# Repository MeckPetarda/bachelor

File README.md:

# Lighthouse — UHF RFID attendance system

Bachelor's thesis project:
**Embedded Implementation of an Attendance System for Integration into an Enterprise Application**

**Author:** Jakub Hloušek
**Supervisor:** Ing. Michal Bastl, Ph.D.
**Institution:** Brno University of Technology, Faculty of Mechanical Engineering
**Academic year:** 2025/26

## Overview

Lighthouse is a passive, hands-free attendance tracking system using UHF RFID technology (860–960 MHz) to detect
employees at 2–3 meter range without any user interaction. Tags are detected through bags, purses, and pockets. Two
paired Lighthouse units at an entrance determine traversal direction (entry vs. exit) and report events to a central
server, which integrates with Navigo3 — a Czech HR/enterprise application by Navigo Solutions s.r.o.

The system is designed to be cost-effective, low-maintenance, and self-contained with its own REST API, while also
supporting external integration.

## Architecture

```text
[UHF RFID Tag] ──► [Lighthouse Unit A] ──► MQTT ──► [Server] ──► [Navigo3 API]
                   [Lighthouse Unit B] ──►          │
                                                    ├── PostgreSQL
                                                    ├── REST API
                                                    └── SolidJS Dashboard
```

The project consists of three major components:

### Firmware (`src/lighthouse/`)

ESP32-based firmware written in C using ESP-IDF and FreeRTOS. Runs on custom PCBs with YPD-R300 UHF RFID reader modules.

Key features:

- UHF RFID tag reading via UART (command 0x89 real-time inventory)
- IR sensor-triggered scan windows
- WiFi provisioning via captive portal (AP mode with DNS redirect)
- MQTT communication with QoS 2 and Last Will & Testament
- NTP time synchronization with explicit quality tracking (`synced`, `estimated`, `relative`)
- Offline event caching on LittleFS (2 MB partition, ~43k events)
- Battery monitoring via ADC
- Health telemetry reporting
- AES-encrypted credential storage in dedicated NVS partition

Firmware source modules: `lighthouse.c`, `rfid_reader.c`, `my_mqtt_client.c`, `io_controller.c`, `battery_monitor.c`,
`time_sync.c`, `wifi_manager.c`, `offline_event_logger.c`, and the `wifi_provisioning` component.

### Server (`src/server/`)

BunJS/TypeScript backend with an embedded MQTT broker.

| Layer    | Technology | Purpose                           |
| -------- | ---------- | --------------------------------- |
| Runtime  | Bun        | TypeScript execution, test runner |
| HTTP     | Hono       | REST API framework                |
| Database | PostgreSQL | Persistent storage                |
| ORM      | Drizzle    | Type-safe queries, migrations     |
| MQTT     | Aedes      | Embedded broker (no external dep) |
| Frontend | SolidJS    | Dashboard SPA                     |
| Build    | Vite       | Frontend bundling                 |

REST API provides endpoints for lighthouses, groups, events, scans, and users. WebSocket support for real-time dashboard
updates. Retention cleanup scheduler for old data. Event sweeper for processing closed RFID scan clusters.

### Hardware (`circuits/lighthouse/`)

Custom PCB designed in KiCad. Board v2 has been sent to fabrication (PCBWay).

Key components: ESP32-WROOM-32, YPD-R300 UHF RFID module, TP4056 charging module (USB-C), SX1308 DC-DC boost converter,
CP2102 USB-UART bridge, 18650 battery holder, IR sensor for scan triggering.

### Dashboard (`src/server/src/web/`)

SolidJS single-page application served by the backend. Pages for lighthouse management, groups, raw events, processed
events, and users.

## Repository structure

```text
.
├── src/
│   ├── lighthouse/          # ESP32 firmware (ESP-IDF/FreeRTOS, C)
│   │   ├── main/            # Core firmware modules
│   │   ├── components/      # WiFi provisioning component (captive portal, settings)
│   │   ├── partitions.csv   # Flash partition layout
│   │   └── sdkconfig        # ESP-IDF configuration
│   └── server/              # Backend + frontend (BunJS, TypeScript, SolidJS)
│       ├── src/
│       │   ├── api/         # Hono REST routes and middleware
│       │   ├── database/    # Drizzle ORM schema and client
│       │   ├── mqtt/        # Aedes broker, topic handlers
│       │   ├── services/    # Event processing, algorithms, Navigo3 integration
│       │   └── web/         # SolidJS dashboard (pages, components, stores)
│       └── tests/           # Bun test suite
├── circuits/lighthouse/     # KiCad PCB project (schematic, board, components)
├── docs/                    # Datasheets, API docs, design documents
├── tasks/                   # Agent task documents (implementation specs)
├── logbook/                 # Development logs
├── write/                   # Thesis LaTeX/Typst sources
├── scripts/                 # Utility scripts (NTP setup)
└── presentation/            # Presentation materials
```

## Prerequisites

### Firmware

- [ESP-IDF](https://docs.espressif.com/projects/esp-idf/en/latest/esp32/get-started/) (v5.x)
- ESP32 development board or Lighthouse custom PCB
- USB-UART connection (CP2102 or external adapter)

### Server

- [Bun](https://bun.sh/) runtime
- PostgreSQL (with a database named `attendance`)
- [chrony](https://chrony-project.org/) NTP server (optional, for ESP32 time sync on LAN — config in
  `src/server/config/chrony.conf`)

## Building & flashing the firmware

### 1. set up ESP-IDF environment

```bash
. /home/kuba/code/esp-idf/export.sh
```

### 2. build

```bash
cd src/lighthouse
idf.py build
```

### 3. flash

The firmware uses a custom partition table. All four binaries must be flashed to their correct offsets:

```bash
esptool --chip esp32 -p /dev/ttyUSB0 -b 921600 \
  --before=no-reset --after=no-reset --no-stub \
  write-flash --flash-mode dio --flash-freq 40m --flash-size detect \
  0x1000 ./build/bootloader/bootloader.bin \
  0x8000 ./build/partition_table/partition-table.bin \
  0x360000 ./build/spiffs.bin \
  0x10000 ./build/lighthouse.bin
```

**Flash layout** (from `partitions.csv`):

| Offset   | Size    | Partition        | Purpose                             |
| -------- | ------- | ---------------- | ----------------------------------- |
| 0x1000   | —       | Bootloader       | ESP-IDF managed                     |
| 0x8000   | 4 KB    | Partition table  | Partition metadata                  |
| 0x9000   | 24 KB   | `nvs`            | System NVS (WiFi calibration, etc.) |
| 0xF000   | 4 KB    | `phy_init`       | RF calibration data                 |
| 0x10000  | 1280 KB | `factory`        | Application firmware                |
| 0x150000 | 2 MB    | `offline_events` | LittleFS — offline RFID event cache |
| 0x350000 | 16 KB   | `nvs_settings`   | Encrypted WiFi/MQTT credentials     |
| 0x360000 | 64 KB   | `spiffs`         | Setup page HTML (captive portal)    |

### 4. monitor serial output

```bash
idf.py -p /dev/ttyUSB0 monitor
```

Or with custom baud rate:

```bash
idf.py -p /dev/ttyUSB0 -b 115200 monitor
```

Exit monitor with `Ctrl+]`.

## Running the server

### 1. install dependencies

```bash
cd src/server
bun install
```

### 2. configure database

The server expects PostgreSQL at `postgresql://postgres:postgres@localhost:5432/attendance` by default. Override with
the `DATABASE_URL` environment variable.

Run Drizzle migrations:

```bash
bunx drizzle-kit push
```

### 3. start the server

Development mode (with file watching):

```bash
bun run dev
```

This starts the HTTP server (with embedded MQTT broker) and serves the API.

### 4. build and serve the dashboard

Development (Vite dev server with HMR):

```bash
bun run dev:web
```

Production build:

```bash
bun run build:web
```

The production build is served automatically by the backend at the root path.

### 5. run tests

```bash
bun test
```

Individual test suites:

```bash
bun test tests/mqtt-broker.test.ts
bun test tests/event-processing.test.ts
bun test tests/api-routes.test.ts
```

## Device setup (First boot)

1. Power on the Lighthouse unit. If no WiFi credentials are stored, it enters setup mode automatically.
2. Long-press BUTTON1 (5 seconds) to force entry into setup mode at any time.
3. Connect to the `Lighthouse-Setup` WiFi network from a phone or computer.
4. A captive portal opens automatically on iOS, Android, Windows, and macOS. On Linux, navigate to `http://192.168.4.1`
   manually.
5. Enter WiFi SSID, password, and MQTT broker IP/port on the setup page.
6. The device tests connectivity, saves encrypted credentials to NVS, and reboots into normal operation.

## Debugging

### Firmware debug tips

- **Serial log levels**: Controlled via `sdkconfig`. Default is `DEBUG`. Use `idf.py menuconfig` under
  `Component config → Log output` to change.
- **RF debug mode**: Compile with `#define RF_DEBUG_MODE` in `lighthouse.c` to enable power sweep, parameter queries,
  and continuous RSSI inventory. This replaces normal operation entirely.
- **Button controls in normal mode**: BUTTON1 starts/stops scanning; BUTTON2 prints statistics to serial.
- **LED indicators**: WiFi status LED, MQTT status LED, and RFID scanning status LED provide visual feedback on GPIO
  pins.
- **Offline event log**: Events are cached in LittleFS at the `offline_events` partition. The log uses a ring buffer
  with CRC32 integrity checks per record.
- **Time quality**: Check serial output for `TIME_QUALITY_SYNCED`, `TIME_QUALITY_ESTIMATED`, or `TIME_QUALITY_NONE` —
  events are tagged with this quality in MQTT payloads as the `timeBasis` field.

### Server debug tips

- **Server logs**: Structured logging via the internal logger. Increase verbosity by editing `src/utils/logger.ts`.
- **MQTT debugging**: The embedded Aedes broker runs alongside the HTTP server. Use any MQTT client (e.g.,
  `mosquitto_sub`) to subscribe to `lighthouse/#` topics for raw traffic inspection.
- **Database inspection**: Connect directly to PostgreSQL. Key tables: `raw_scans` (immutable audit log),
  `processed_events` (derived entry/exit), `lighthouses`, `tag_assignments`, `users`.
- **Integration test**: `bun run scripts/integration-test.ts` exercises the MQTT → database pipeline.

### NTP setup

The server machine doubles as the NTP server for Lighthouse devices on the LAN. Install and configure chrony using the
provided config:

```bash
sudo cp src/server/config/chrony.conf /etc/chrony/chrony.conf
sudo systemctl restart chrony
```

Alternatively, use the setup script:

```bash
sudo bash scripts/setup-ntp.sh
```

## Documentation

- `docs/` — Component datasheets (ESP32, R300 RFID module, TP4056, CP2102, etc.)
- `docs/navigo_api.md` — Navigo3 REST API documentation
- `docs/phase2_event_processing_plan.md` — Direction detection algorithm design
- `docs/phase4_integration.md` — Navigo3 integration plan
- `logbook/` — Chronological development logs
- `tasks/` — Structured implementation task documents

## License

See [LICENSE](LICENSE).

---

esp.py build

esptool --chip esp32 -p /dev/ttyUSB0 -b 921600 --before=no-reset --after=no-reset --no-stub write-flash --flash-mode dio
--flash-freq 40m --flash-size detect 0x1000 ./build/bootloader/bootloader.bin 0x8000
./build/partition_table/partition-table.bin 0x360000 ./build/spiffs.bin 0x10000 ./build/lighthouse.bin

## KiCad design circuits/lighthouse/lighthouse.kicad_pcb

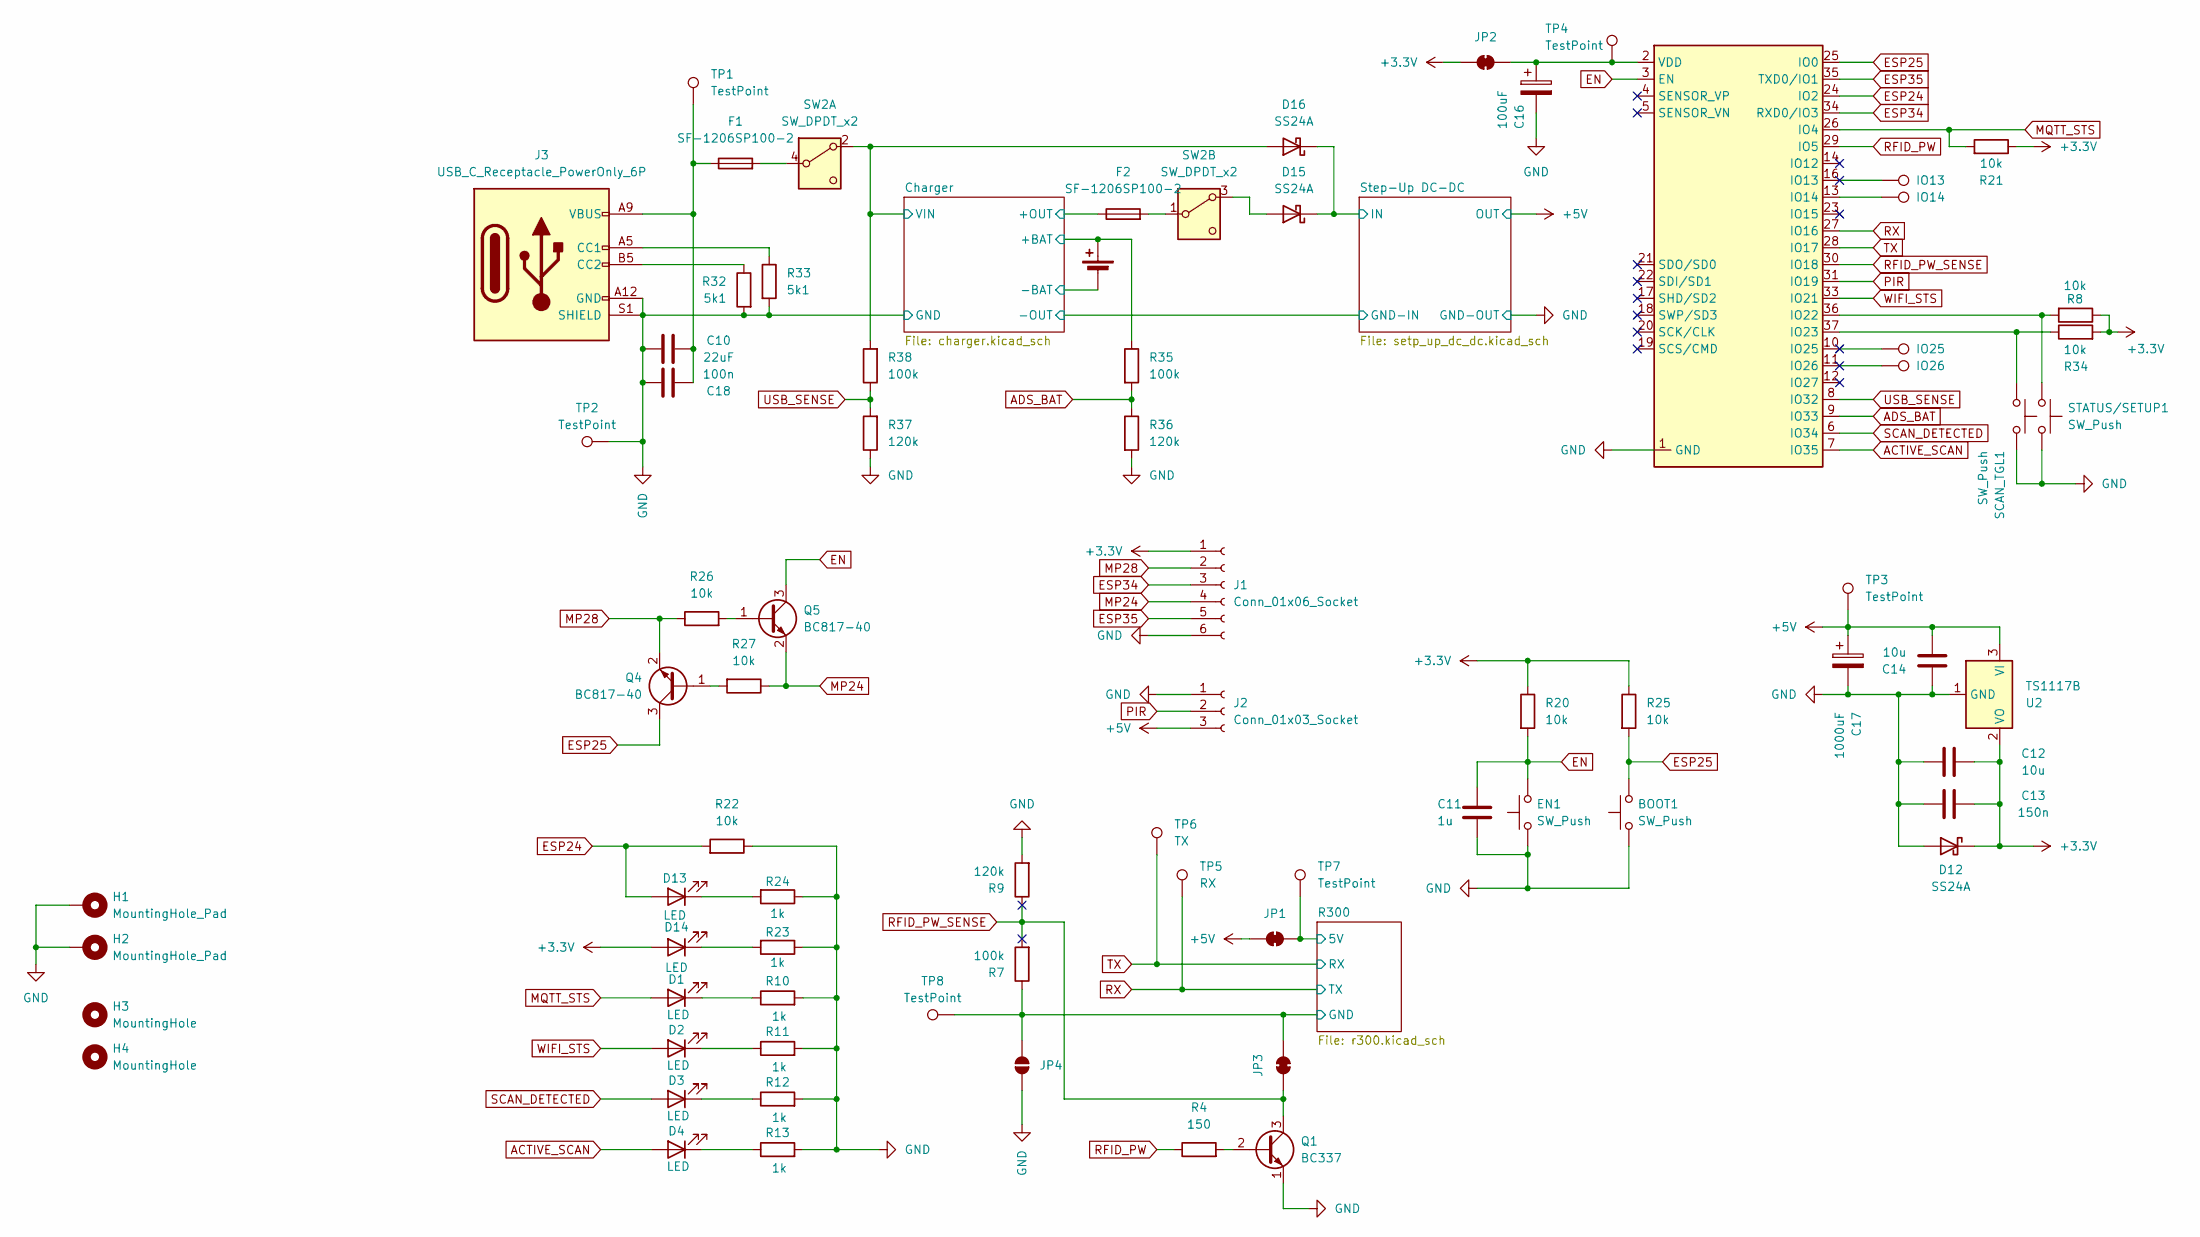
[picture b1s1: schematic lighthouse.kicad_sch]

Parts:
BOOT1: SW_Push; SW_Push_SPST_NO_Alps_SKRK
BT1: Battery_Cell; BatteryHolder_MPD_BH-18650-PC
C10: 22uF; C_1206_3216Metric_Pad1.33x1.80mm_HandSolder
C11: 1u; C_1206_3216Metric_Pad1.33x1.80mm_HandSolder
C12, C14: 10u; C_1206_3216Metric_Pad1.33x1.80mm_HandSolder
C13: 150n; C_1206_3216Metric_Pad1.33x1.80mm_HandSolder
C16: 100uF; CP_Radial_D6.3mm_P2.50mm
C17: 1000uF; CP_Radial_D10.0mm_P5.00mm
C18: 100n; C_1206_3216Metric_Pad1.33x1.80mm_HandSolder
D1, D2, D3, D4: LED; LED_D3.0mm
D12, D15, D16: SS24A; D_SMA
D13, D14: LED; LED_1206_3216Metric_Pad1.42x1.75mm_HandSolder
EN1: SW_Push; SW_Push_SPST_NO_Alps_SKRK
F1, F2: SF-1206SP100-2; Fuse_2920_7451Metric_Pad2.10x5.45mm_HandSolder
H1, H2: MountingHole_Pad; MountingHole_3.2mm_M3_Pad_Via
H3, H4: MountingHole; MountingHole_3.2mm_M3
IO13: GPIO13; TestPoint_Pad_D1.0mm
IO14: GPIO14; TestPoint_Pad_D1.0mm
IO25: GPIO25; TestPoint_Pad_D1.0mm
IO26: GPIO26; TestPoint_Pad_D1.0mm
J1: Conn_01x06_Socket; PinHeader_2x03_P2.00mm_Vertical
J2: Conn_01x03_Socket; JST_XH_B3B-XH-A_1x03_P2.50mm_Vertical
J3: USB_C_Receptacle_PowerOnly_6P; USB_C_Receptacle_HRO_TYPE-C-31-M-17
JP1, JP2, JP3: SolderJumper_2_Bridged; SolderJumper-2_P1.3mm_Bridged2Bar_RoundedPad1.0x1.5mm
JP4: SolderJumper_2_Open; SolderJumper-2_P1.3mm_Open_RoundedPad1.0x1.5mm
Q1: BC337; TO-92_Inline
Q4, Q5: BC817-40; SOT-23
R4: 150; R_1206_3216Metric_Pad1.30x1.75mm_HandSolder
R7, R35, R38: 100k; R_1206_3216Metric_Pad1.30x1.75mm_HandSolder
R8, R20, R21, R22, R25, R26, R27, R34: 10k; R_1206_3216Metric_Pad1.30x1.75mm_HandSolder
R9, R36, R37: 120k; R_1206_3216Metric_Pad1.30x1.75mm_HandSolder
R10, R11, R12, R13, R23, R24: 1k; R_1206_3216Metric_Pad1.30x1.75mm_HandSolder
R32, R33: 5k1; R_1206_3216Metric_Pad1.30x1.75mm_HandSolder
SCAN_TGL1: SW_Push; SW_Push_SPST_NO_Alps_SKRK
STATUS/SETUP1: SW_Push; SW_Push_SPST_NO_Alps_SKRK
SW2: SW_DPDT_x2; JST_XH_B4B-XH-A_1x04_P2.50mm_Vertical
TP1, TP2, TP3, TP4, TP7, TP8: TestPoint; TestPoint_Pad_D1.0mm
TP5: RX; TestPoint_Pad_D1.0mm
TP6: TX; TestPoint_Pad_D1.0mm
U2: TS1117B; SOT-223-3_TabPin2
U7: ESP32-WROOM-32

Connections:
+3.3V: C12.1, C13.1, D12.1 (K), D14.2 (A), J1.1, JP2.1 (A), R8.1, R20.1, R21.1, R25.1, R34.2, U2.2 (VO)
+5V: C14.2, C17.1, J2.3, JP1.1 (A), TP3.1, U2.3 (VI); also elsewhere on the board
/Charger/+BAT: BT1.1 (+), F2.1, R35.1; also elsewhere on the board
/Charger/-BAT: BT1.2 (-); also elsewhere on the board
/Charger/VIN: D16.2 (A), R38.2, SW2.2 (A); also elsewhere on the board
/R300/5V: JP1.2 (B), TP7.1; also elsewhere on the board
/R300/GND: JP3.2 (B), JP4.2 (B), R7.1, TP8.1; also elsewhere on the board
/Step-Up DC-DC/IN: D15.1 (K), D16.1 (K); also elsewhere on the board
ACTIVE_SCAN: D4.2 (A), U7.7 (IO35)
ADS_BAT: R35.2, R36.1, U7.9 (IO33)
EN: C11.1, EN1.2, Q5.3 (C), R20.2, U7.3 (EN)
ESP24: D13.2 (A), R22.2, U7.24 (IO2)
ESP25: BOOT1.2, Q4.3 (C), R25.2, U7.25 (IO0)
ESP34: J1.3, U7.34 (RXD0/IO3)
ESP35: J1.5, U7.35 (TXD0/IO1)
GND: BOOT1.1, C10.2, C11.2, C12.2, C13.2, C14.1, C16.2, C17.2, C18.2, D12.2 (A), EN1.1, H1.1, H2.1, J1.6, J2.1, J3.A12 (GND), J3.B12 (GND), J3.S1 (SHIELD), JP4.1 (A), Q1.1 (E), R9.2, R10.2, R11.2, R12.2, R13.2, R22.1, R23.1, R24.1, R32.2, R33.2, R36.2, R37.1, SCAN_TGL1.1, STATUS/SETUP1.1, TP2.1, U2.1 (GND), U7.1 (GND), U7.15 (GND), U7.32 (NC), U7.38 (GND), U7.39 (GND); also elsewhere on the board
MP24: J1.4, Q5.2 (E), R27.1
MP28: J1.2, Q4.2 (E), R26.1
MQTT_STS: D1.2 (A), R21.2, U7.26 (IO4)
unnamed: C10.1, C18.1, F1.1, J3.A9 (VBUS), J3.B9 (VBUS), TP1.1
unnamed: D1.1 (K), R10.1
unnamed: D2.1 (K), R11.1
unnamed: D3.1 (K), R12.1
unnamed: D4.1 (K), R13.1
unnamed: D13.1 (K), R24.2
unnamed: D14.1 (K), R23.2
unnamed: D15.2 (A), SW2.3 (A)
unnamed: J3.A5 (CC1), R33.1
unnamed: J3.B5 (CC2), R32.1
unnamed: C16.1, JP2.2 (B), TP4.1, U7.2 (VDD)
unnamed: Q1.2 (B), R4.2
unnamed: Q4.1 (B), R27.2
unnamed: Q5.1 (B), R26.2
unnamed: F1.2, SW2.4 (B)
unnamed: F2.2, SW2.1 (B)
unnamed: IO14.1, U7.13 (IO14)
unnamed: R8.2, STATUS/SETUP1.2, U7.36 (IO22)
unnamed: R34.1, SCAN_TGL1.2, U7.37 (IO23)
PIR: J2.2, U7.31 (IO19)
RFID_PW: R4.1, U7.29 (IO5)
RFID_PW_SENSE: JP3.1 (A), Q1.3 (C), R7.2, R9.1, U7.30 (IO18)
RX: TP5.1, U7.27 (IO16); also elsewhere on the board
SCAN_DETECTED: D3.2 (A), U7.6 (IO34)
TX: TP6.1, U7.28 (IO17); also elsewhere on the board
USB_SENSE: R37.2, R38.1, U7.8 (IO32)
WIFI_STS: D2.2 (A), U7.33 (IO21)

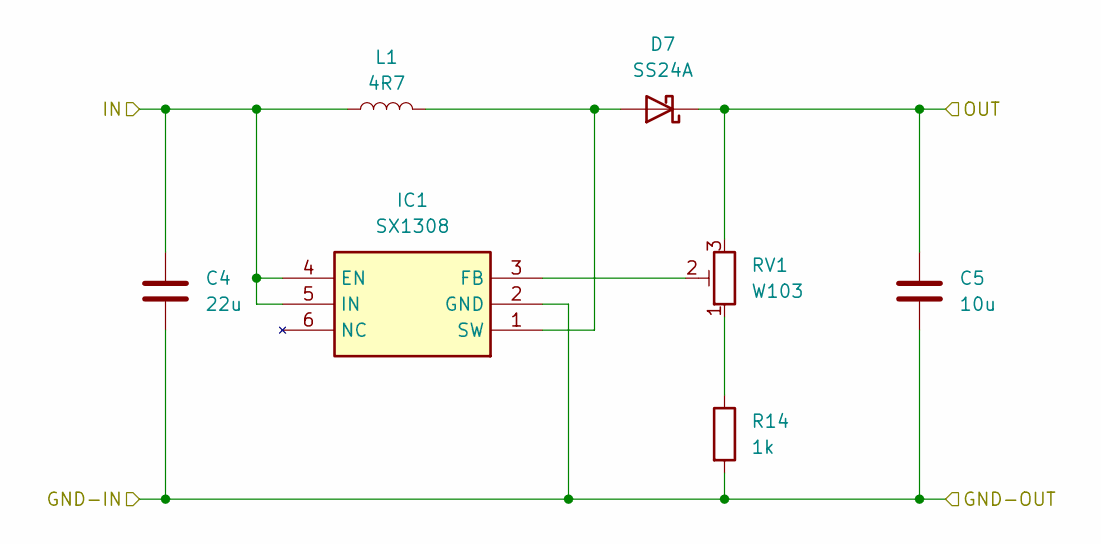
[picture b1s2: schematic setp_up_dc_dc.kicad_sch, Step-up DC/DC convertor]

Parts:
C4: 22u; C_1206_3216Metric_Pad1.33x1.80mm_HandSolder
C5: 10u; C_1206_3216Metric_Pad1.33x1.80mm_HandSolder
D7: SS24A; D_SMA
IC1: SX1308; SOT95P280X145-6N; Manufacturer_Part_Number SX1308
L1: 4R7; IDCP2218ER101M01
R14: 1k; R_1206_3216Metric_Pad1.30x1.75mm_HandSolder
RV1: W103; 3296W1503LF

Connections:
+5V: C5.1, D7.1 (K), RV1.3; also elsewhere on the board
/Step-Up DC-DC/IN: C4.1, IC1.4 (EN), IC1.5 (IN), L1.1; also elsewhere on the board
GND: C4.2, C5.2, IC1.2 (GND), R14.2; also elsewhere on the board
unnamed: D7.2 (A), IC1.1 (SW), L1.2
unnamed: IC1.3 (FB), RV1.2
unnamed: R14.1, RV1.1

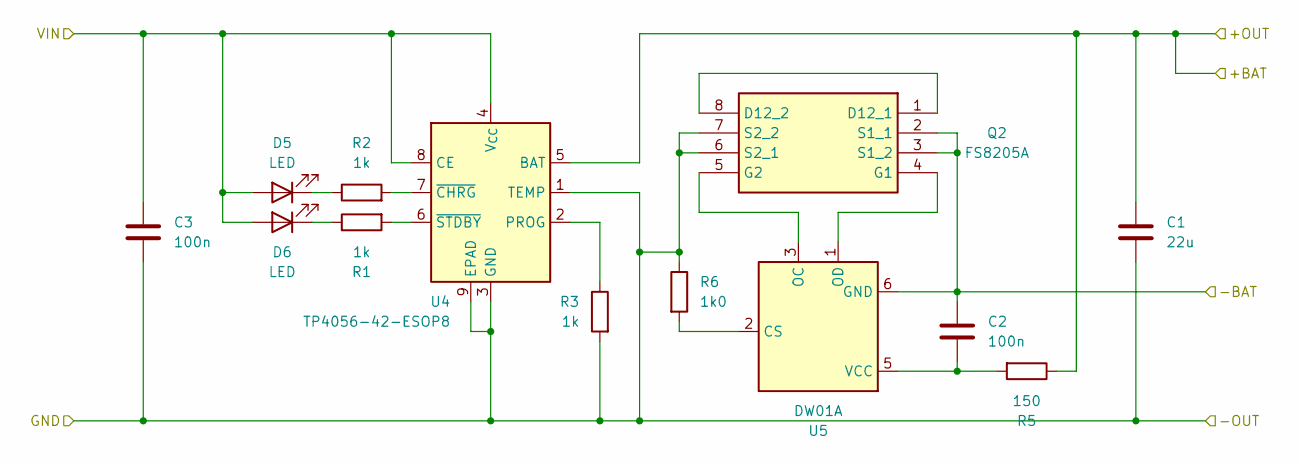
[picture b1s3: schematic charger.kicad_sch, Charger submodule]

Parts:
C1: 22u; C_1206_3216Metric_Pad1.33x1.80mm_HandSolder
C2, C3: 100n; C_1206_3216Metric_Pad1.33x1.80mm_HandSolder
D5, D6: LED; LED_1206_3216Metric_Pad1.42x1.75mm_HandSolder
Q2: FS8205A; SOP65P640X120-8N; Manufacturer_Part_Number FS8205A
R1, R2, R3: 1k; R_1206_3216Metric_Pad1.30x1.75mm_HandSolder
R5: 150; R_1206_3216Metric_Pad1.30x1.75mm_HandSolder
R6: 1k0; R_1206_3216Metric_Pad1.30x1.75mm_HandSolder
U4: TP4056-42-ESOP8; SOIC-8-1EP_3.9x4.9mm_P1.27mm_EP2.41x3.3mm_ThermalVias
U5: DW01A; SOT-23-6

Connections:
/Charger/+BAT: C1.1, R5.1, U4.5 (BAT); also elsewhere on the board
/Charger/-BAT: C2.2, Q2.2 (S1_1), Q2.3 (S1_2), U5.6 (GND); also elsewhere on the board
/Charger/VIN: C3.1, D5.2 (A), D6.2 (A), U4.4 (V_{CC}), U4.8 (CE); also elsewhere on the board
GND: C1.2, C3.2, Q2.6 (S2_1), Q2.7 (S2_2), R3.2, R6.1, U4.1 (TEMP), U4.3 (GND), U4.9 (EPAD); also elsewhere on the board
unnamed: D5.1 (K), R2.1
unnamed: D6.1 (K), R1.1
unnamed: Q2.1 (D12_1), Q2.8 (D12_2)
unnamed: Q2.4 (G1), U5.1 (OD)
unnamed: Q2.5 (G2), U5.3 (OC)
unnamed: R3.1, U4.2 (PROG)
unnamed: R2.2, U4.7 (~CHRG)
unnamed: R1.2, U4.6 (~STDBY)
unnamed: R6.2, U5.2 (CS)
unnamed: C2.1, R5.2, U5.5 (VCC)

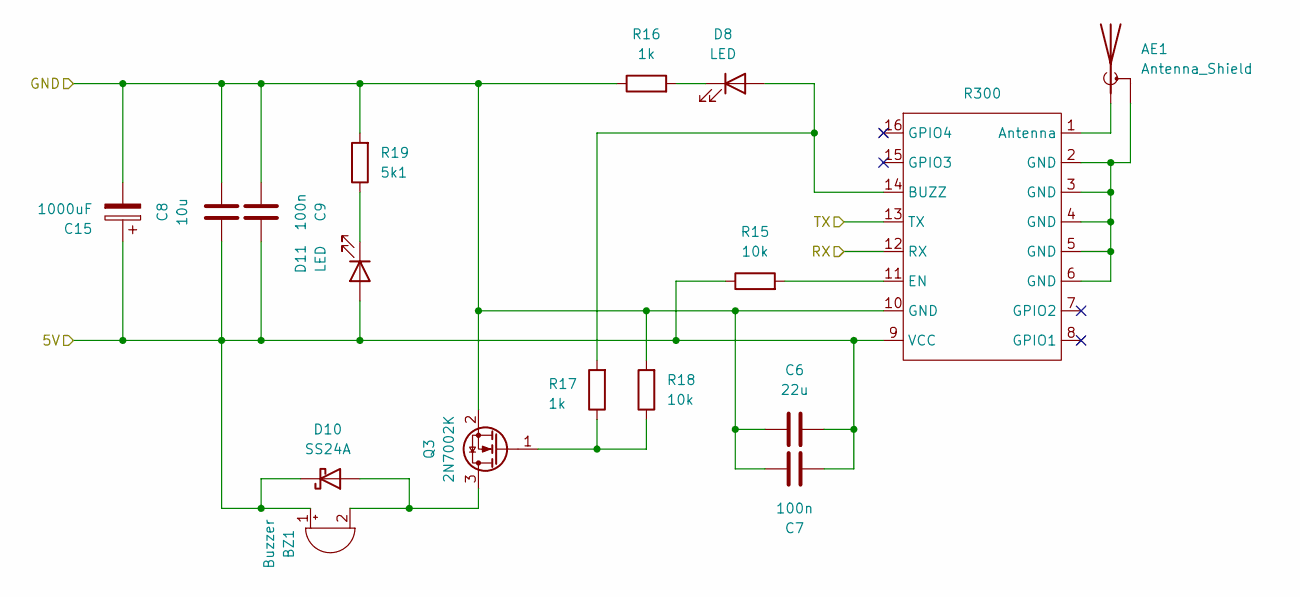
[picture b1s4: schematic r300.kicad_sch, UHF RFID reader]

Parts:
AE1: Antenna_Shield; SMA_Samtec_SMA-J-P-H-ST-EM1_EdgeMount
BZ1: Buzzer; Buzzer_12x9.5RM7.6
C6: 22u; C_1206_3216Metric_Pad1.33x1.80mm_HandSolder
C7, C9: 100n; C_1206_3216Metric_Pad1.33x1.80mm_HandSolder
C8: 10u; C_1206_3216Metric_Pad1.33x1.80mm_HandSolder
C15: 1000uF; CP_Radial_D10.0mm_P5.00mm
D8, D11: LED; LED_1206_3216Metric_Pad1.42x1.75mm_HandSolder
D10: SS24A; D_SMA
Q3: 2N7002K; SOT-23
R15, R18: 10k; R_1206_3216Metric_Pad1.30x1.75mm_HandSolder
R16, R17: 1k; R_1206_3216Metric_Pad1.30x1.75mm_HandSolder
R19: 5k1; R_1206_3216Metric_Pad1.30x1.75mm_HandSolder
U1: R300

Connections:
/R300/5V: BZ1.1 (+), C6.2, C7.2, C8.1, C9.1, C15.1, D10.1 (K), D11.2 (A), R15.1, U1.9 (VCC); also elsewhere on the board
/R300/GND: C6.1, C7.1, C8.2, C9.2, C15.2, Q3.2 (S), R16.1, R18.2, R19.2, U1.10 (GND); also elsewhere on the board
unnamed: AE1.1 (A), U1.1 (Antenna)
unnamed: AE1.2 (Shield), U1.2 (GND), U1.3 (GND), U1.4 (GND), U1.5 (GND), U1.6 (GND)
unnamed: BZ1.2 (-), D10.2 (A), Q3.3 (D)
unnamed: D8.2 (A), R17.2, U1.14 (BUZZ)
unnamed: D8.1 (K), R16.2
unnamed: D11.1 (K), R19.1
unnamed: Q3.1 (G), R17.1, R18.1
unnamed: R15.2, U1.11 (EN)
RX: U1.13 (TX); also elsewhere on the board
TX: U1.12 (RX); also elsewhere on the board

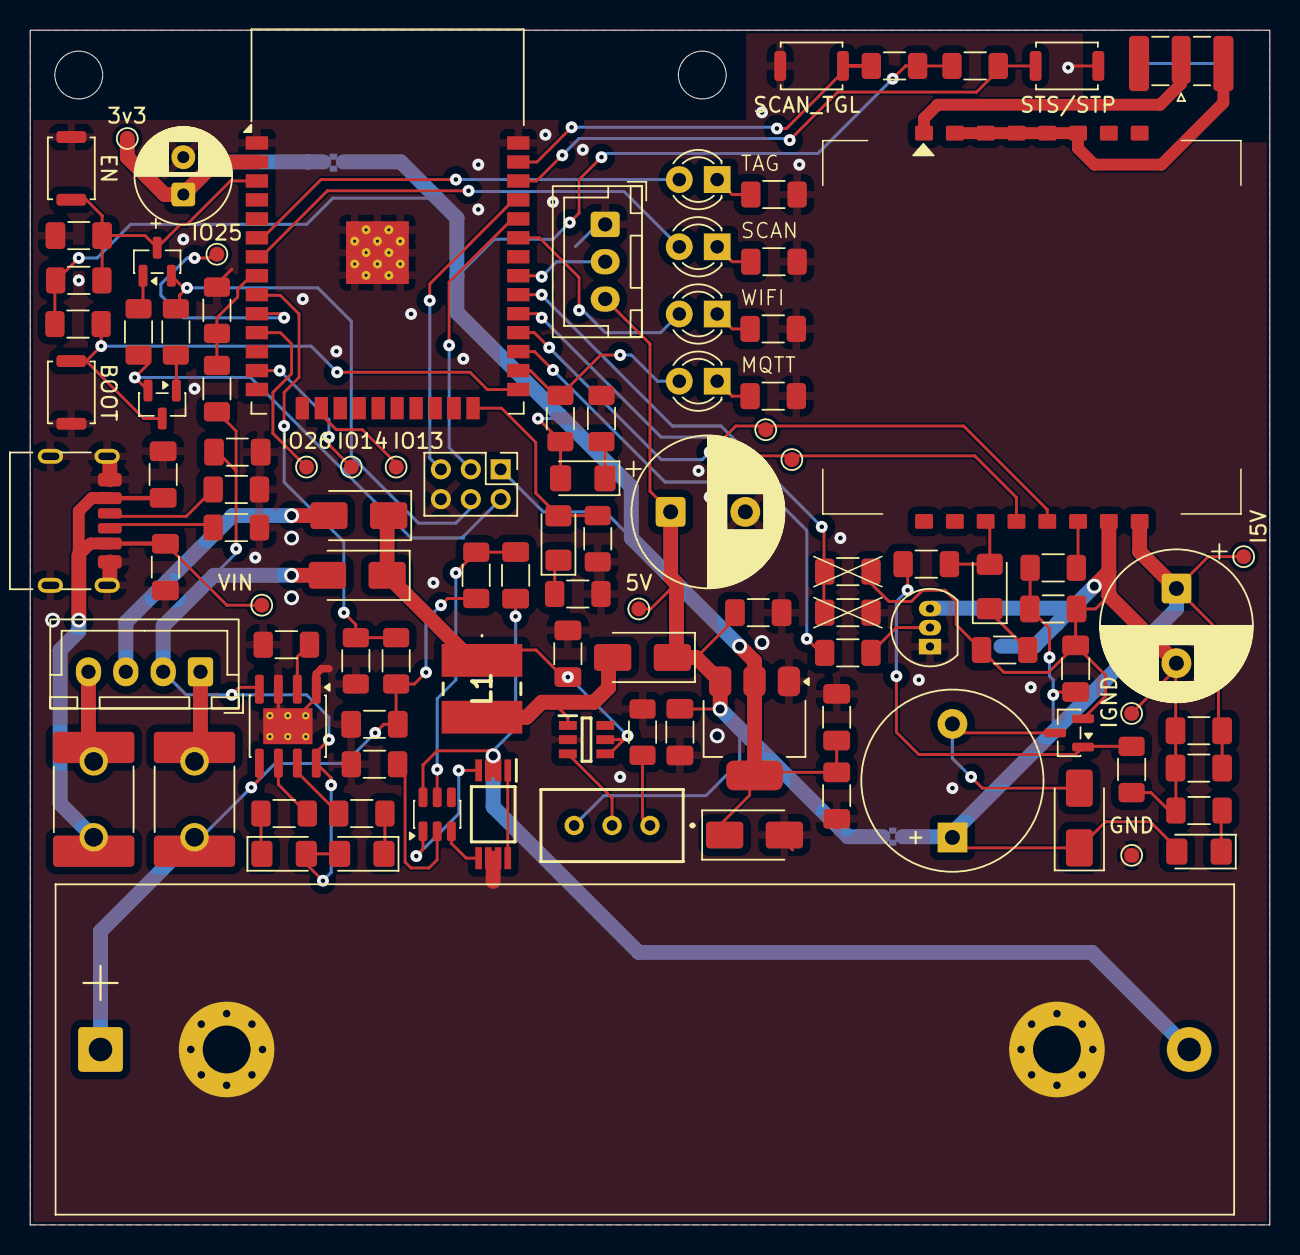
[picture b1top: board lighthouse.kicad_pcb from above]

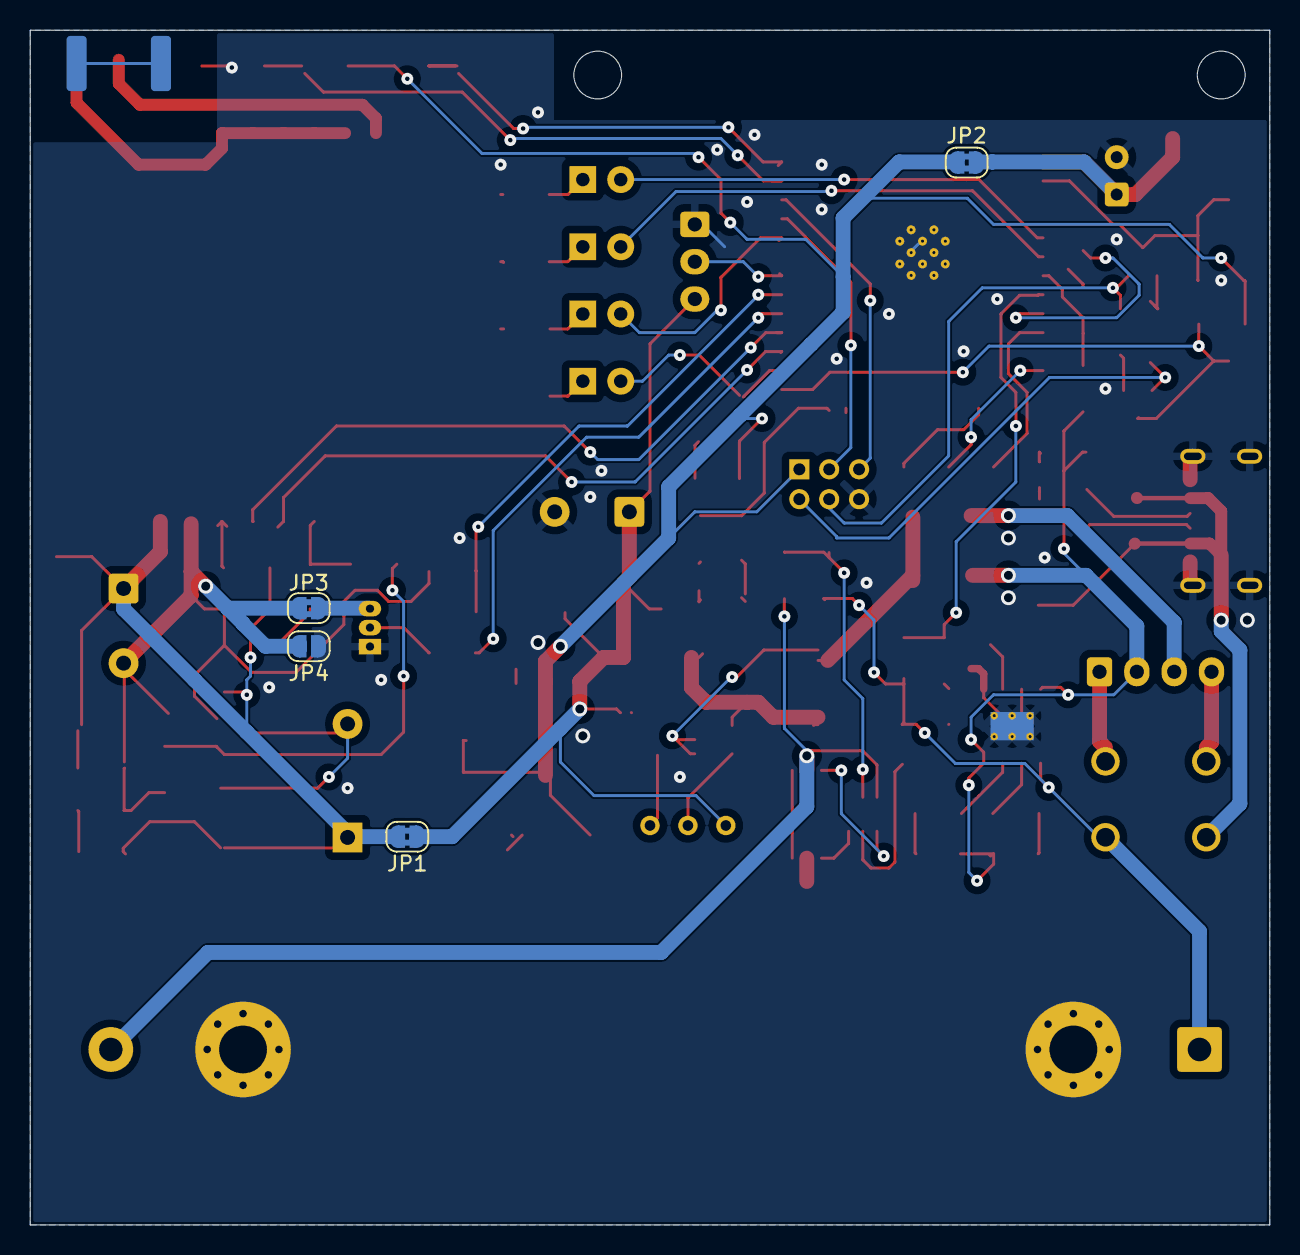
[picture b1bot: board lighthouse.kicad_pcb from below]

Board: 2 copper layers, 83.0 x 80.0 mm, 113 parts (4 on the bottom side), 67 nets.

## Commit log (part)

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2025-12-07 Added first devlog entry
2025-12-15 Added docs
2025-12-16 PoC with the rfid reader connected via UART
2025-12-18 Disabled PIR sensor for now
2025-12-18 Removed old command
2025-12-18 Finalized 0x8B documentation
2025-12-18 Truncate devlogs to essential technical content
    Reduced all devlogs to 70-150 lines by:
    - Removing code snippets (git tracks code)
    - Removing verbose explanations and rambling
    - Consolidating technical details
    - Removing information duplicated in docs
    - Keeping only concrete technical facts
2025-12-20 Implement WiFi Station Mode PoC for ESP32
    Added complete WiFi connectivity support based on ESP32_WiFi_Setup_Research.md:
    Components:
    - wifi_manager.h: Public API for WiFi management with configuration
    - wifi_manager.c: Full implementation with event-driven architecture
    * NVS flash initialization for persistent config
    * ESP-NETIF and lwIP TCP/IP stack setup
2025-12-21 Added MQTT implementation roadmap
2025-12-21 Stabilized MQTT PoC
2025-12-22 KiCAD experimets & pin fixes to acomedate wiring changes
2025-12-23 Added offline event log implementation details
2025-12-24 Fixed dependencies
2025-12-24 Added addendum to reader healthcheck task
2025-12-24 Removed old and obsolete code
2025-12-24 Created reader_healthcheck task addendum 2.
2025-12-27 Add MQTT health metrics publishing on statistics button press
    When BUTTON2 (statistics log button) is pressed, the device now:
    1. Displays RFID statistics to console (existing behavior)
    2. Publishes health metrics via MQTT (new behavior)
    Health metrics include:
    - System memory (free heap)
    - System uptime
2025-12-27 Update Dec 25 devlog: document relay experiment and reversion
    - Document dual power sensing relay experiment and mixed results
    - Capture lessons learned: relay contact bounce caused unreliable readings
    - Update to reflect reversion to single GPIO 2 power check
    - Note transistor (BC337) parts ordered for improved design
    - Simplify state machine and health struct to match current implementation
2025-12-30 Server boilerplate
2025-12-30 Implement PostgreSQL connection pool (Task 1.3)
    - Enhanced database client with robust error handling and logging
    - Added query helper functions (executeQuery, withTransaction, rawQuery)
    - Implemented graceful shutdown with SIGINT/SIGTERM handlers
    - Added connection test that queries lighthouses table on startup
    - Added health check and pool statistics functions
    - Updated tsconfig to include Bun types
2025-12-30 Added a simple logger
2025-12-30 Implement REST API endpoints (Task 1.5)
    Add basic REST API infrastructure with Hono framework:
    - JWT authentication middleware with token creation/verification
    - Request logging and error handling middleware
    - Health check endpoint with service status
    - Login endpoint with password verification
    - Lighthouse CRUD endpoints (list, create, get, update)
2026-01-05 Added wifi wifi provisioning plan
2026-01-05 Add WiFi settings storage implementation (Phase 1, Step 1.3)
    Implements encrypted credential storage using AES-128-ECB and NVS:
    - wifi_settings_init(): Initialize NVS partition for WiFi settings
    - wifi_settings_is_configured(): Check if device has saved credentials
    - wifi_settings_load(): Decrypt and load credentials from NVS
    - wifi_settings_save(): Encrypt and save credentials to NVS
    - wifi_settings_factory_reset(): Erase all WiFi configuration
2026-01-05 Removed implementation code from implementation plan
2026-01-05 Fixed component config
2026-01-06 Added phase 3 plan
2026-01-06 Fixed imports
2026-01-07 Adding wifi provisioning addendum
2026-01-24 Fix WiFi provisioning client disconnect and init errors
    Issue A: Browser disconnects during WiFi test
    - Create STA netif during AP initialization (not just at test time)
    - Switch to APSTA mode without stopping WiFi (preserves AP client connections)
    - Use esp_wifi_connect() instead of stop/start cycle
    - On test failure, just switch back to AP mode without restart
    Issue B: WiFi manager fails to initialize after provisioning
2026-01-24 Fix WiFi not connecting on first boot after provisioning
    When WiFi was already started by provisioning, calling esp_wifi_start()
    again doesn't trigger WIFI_EVENT_STA_START, so the event handler's
    esp_wifi_connect() call never happens.
    Fix: Explicitly call esp_wifi_connect() after esp_wifi_start() to
    ensure connection is initiated regardless of whether the event fires.
    The event handler may also call connect, but calling it twice is safe
2026-01-25 Added captive portal setup page
    Implement WiFi captive portal for automatic setup page
    Add DNS server and HTTP wildcard handler to enable automatic captive portal
    detection on connected devices. When a device connects to the provisioning AP,
    the OS detects the captive portal and automatically opens the setup page.
    Changes:
    - Add dns_server.h/c: UDP DNS server on port 53 that responds to all queries
2026-01-25 Add unique message ID to acknowledgment system
    - Generate unique ack_id for each /configure response
    - Include ack_id in JSON response to browser
    - Browser sends ack_id back in POST /ack request
    - ESP verifies ack_id matches before accepting acknowledgment
    - Prevents stale or out-of-order acknowledgments from being accepted
2026-01-27 Made "wifi storage" into a more general "settings storage" & improved setup statemachine
2026-01-28 Added mqtt topics standardization task
2026-01-28 Implement firmware MQTT topic standardization (Tasks 12-14)
    Task 12 - MAC Address Retrieval and Topic Building:
    - Remove hardcoded MQTT_CLIENT_ID, topic defines from header
    - Add MQTT_TOPIC_BASE and MQTT_MAC_STR_LEN defines
    - Add mqtt_client_get_device_mac() to retrieve formatted MAC
    - Add mqtt_client_get_topic() for dynamic topic building
    - Initialize MAC via esp_efuse_mac_get_default() at startup
2026-01-28 Fixed database schema
2026-01-29 Implement GPIO pin migration for RFID power control
    Migrate power rail sensing from GPIO2 (strapping pin) to GPIO22 to
    eliminate firmware flashing conflicts. Add RFID reader transistor
    control on GPIO5 for power management.
    Changes:
    - uart_reader.h: Add RFID_POWER_CONTROL_PIN (GPIO5) and rename
    POWER_STATUS_PIN to POWER_SENSE_PIN (GPIO22)
2026-01-30 Fixed migration
2026-01-30 Fix test cleanup to include all test lighthouses
    The tests that check group member limits create "Group Member 1" and
    "Group Member 2" lighthouses which weren't being cleaned up between
    tests, causing unique constraint violations.
    https://claude.ai/code/session_01GCjjtv9afa3TFbT9g4Uy4V
2026-01-31 Fix Vite proxy to not intercept source module imports
    Changed proxy from /api to /api/v1 to prevent the proxy
    from intercepting imports of the api/ source folder.
    https://claude.ai/code/session_01GnvTdsbR9yRPU4s7fuGpmr
2026-02-01 Kicad greatness
2026-02-05 Reverse engineered cell charger (component values missing)
2026-02-10 More circuits
2026-02-21 Added rogue chip docs
2026-02-22 Rewamped the pcb
2026-02-22 Cleaned up schematics
2026-02-22 Pre-pin reassignment commit
2026-02-23 Added YR300 model
2026-02-24 Added PSBWAY's constraints (currently valid)
2026-02-24 Added today's devlog
2026-02-25 Added battery_sense task
2026-02-26 Added usb power sense to schematic, pcb pending
2026-02-26 Safekeeping
2026-03-02 Added IR task assignment
2026-03-03 Added ir reader latency task
2026-03-03 feat(rfid): disable reader buzzer on startup via set_beeper_mode
    Implements R300 protocol command 0x7A (cmd_name_set_beeper_mode) to
    silence the reader buzzer during normal inventory operation. On
    successful handshake at init time the module is configured to
    R300_BEEPER_MODE_QUIET (0x00), which is persisted to internal flash
    across power cycles (Protocol V2.2, Section 2.1.11). Failure to set
    the mode is non-fatal: a LOGW is emitted and initialization continues.
2026-03-03 Reverted scanning interval changes
2026-03-10 Made pin mappings production ready (in firmware, board patch pending)
2026-03-15 Added IO improvement task
2026-03-16 Added cahce purge task
2026-03-16 Renamed uart_reader to rfid_reader
2026-03-16 Added io refactor task
2026-03-17 Fixed faulty reader health reporting
2026-03-17 feat(firmware): implement SNTP time sync module and timeBasis-aware MQTT payloads
    Task 2 — SNTP Time Sync Module:
    - Add time_sync.h / time_sync.c with TIME_QUALITY_NONE/ESTIMATED/SYNCED states
    - SNTP init using MQTT broker IP (same host as NTP daemon) as server address
    - NVS persistence (namespace "time_sync") for last-known-good time across boots
    - Boot with NVS time → TIME_QUALITY_ESTIMATED; first boot → TIME_QUALITY_NONE
    - Sync callback upgrades to TIME_QUALITY_SYNCED and persists to NVS
2026-03-19 Users page PoC
2026-03-19 Users mock api/page/store
2026-03-20 Phase 2 - Task 1 - db migration
2026-03-20 Phase 2 - Task 5 - RSSI algorithm
2026-03-20 Phase 2 - Task 8 - Wiring it together
2026-03-20 Removed old migrations
2026-03-21 Logger adjustments
2026-03-22 RFID debug mode
2026-03-22 Switched to real-time scanning, the transfer protocol gets overwhelmed and need a redesign
2026-03-22 Removed ugly long hyphens
2026-03-22 Implement LED indicator and Button 1 behaviour refactor (io_improvement_task)
2026-03-23 Bookkeeping
2026-04-14 Working model
2026-04-15 Outlie plus 3.x
2026-04-16 Chapter 2 draft 2
2026-04-17 Sumbol cleanup
2026-04-21 Reorganized invoicing
2026-05-02 Expanding outline to prose first draft of most of chapter 3
2026-05-11 Unknown model change
2026-05-11 Improved offline replay
2026-05-12 Finalized offline event sync
2026-05-12 Fixed conclustion's outline
2026-05-13 Fixing figures and tables
2026-05-14 Finalized circuit attachments
2026-05-14 Removed last placeholder figures
2026-05-16 All mechanical drawings done
2026-05-16 Expanded file is now the main
2026-05-18 Fixed pdfs with ghostscript
2026-05-20 Fixed PCB schematic reference
